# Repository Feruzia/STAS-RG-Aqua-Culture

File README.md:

# STAS-RG-Aqua-Culture
The home base for STAS-RG Aqua Culture research. Covering everything from PCBs and ESP32 code to machine learning.

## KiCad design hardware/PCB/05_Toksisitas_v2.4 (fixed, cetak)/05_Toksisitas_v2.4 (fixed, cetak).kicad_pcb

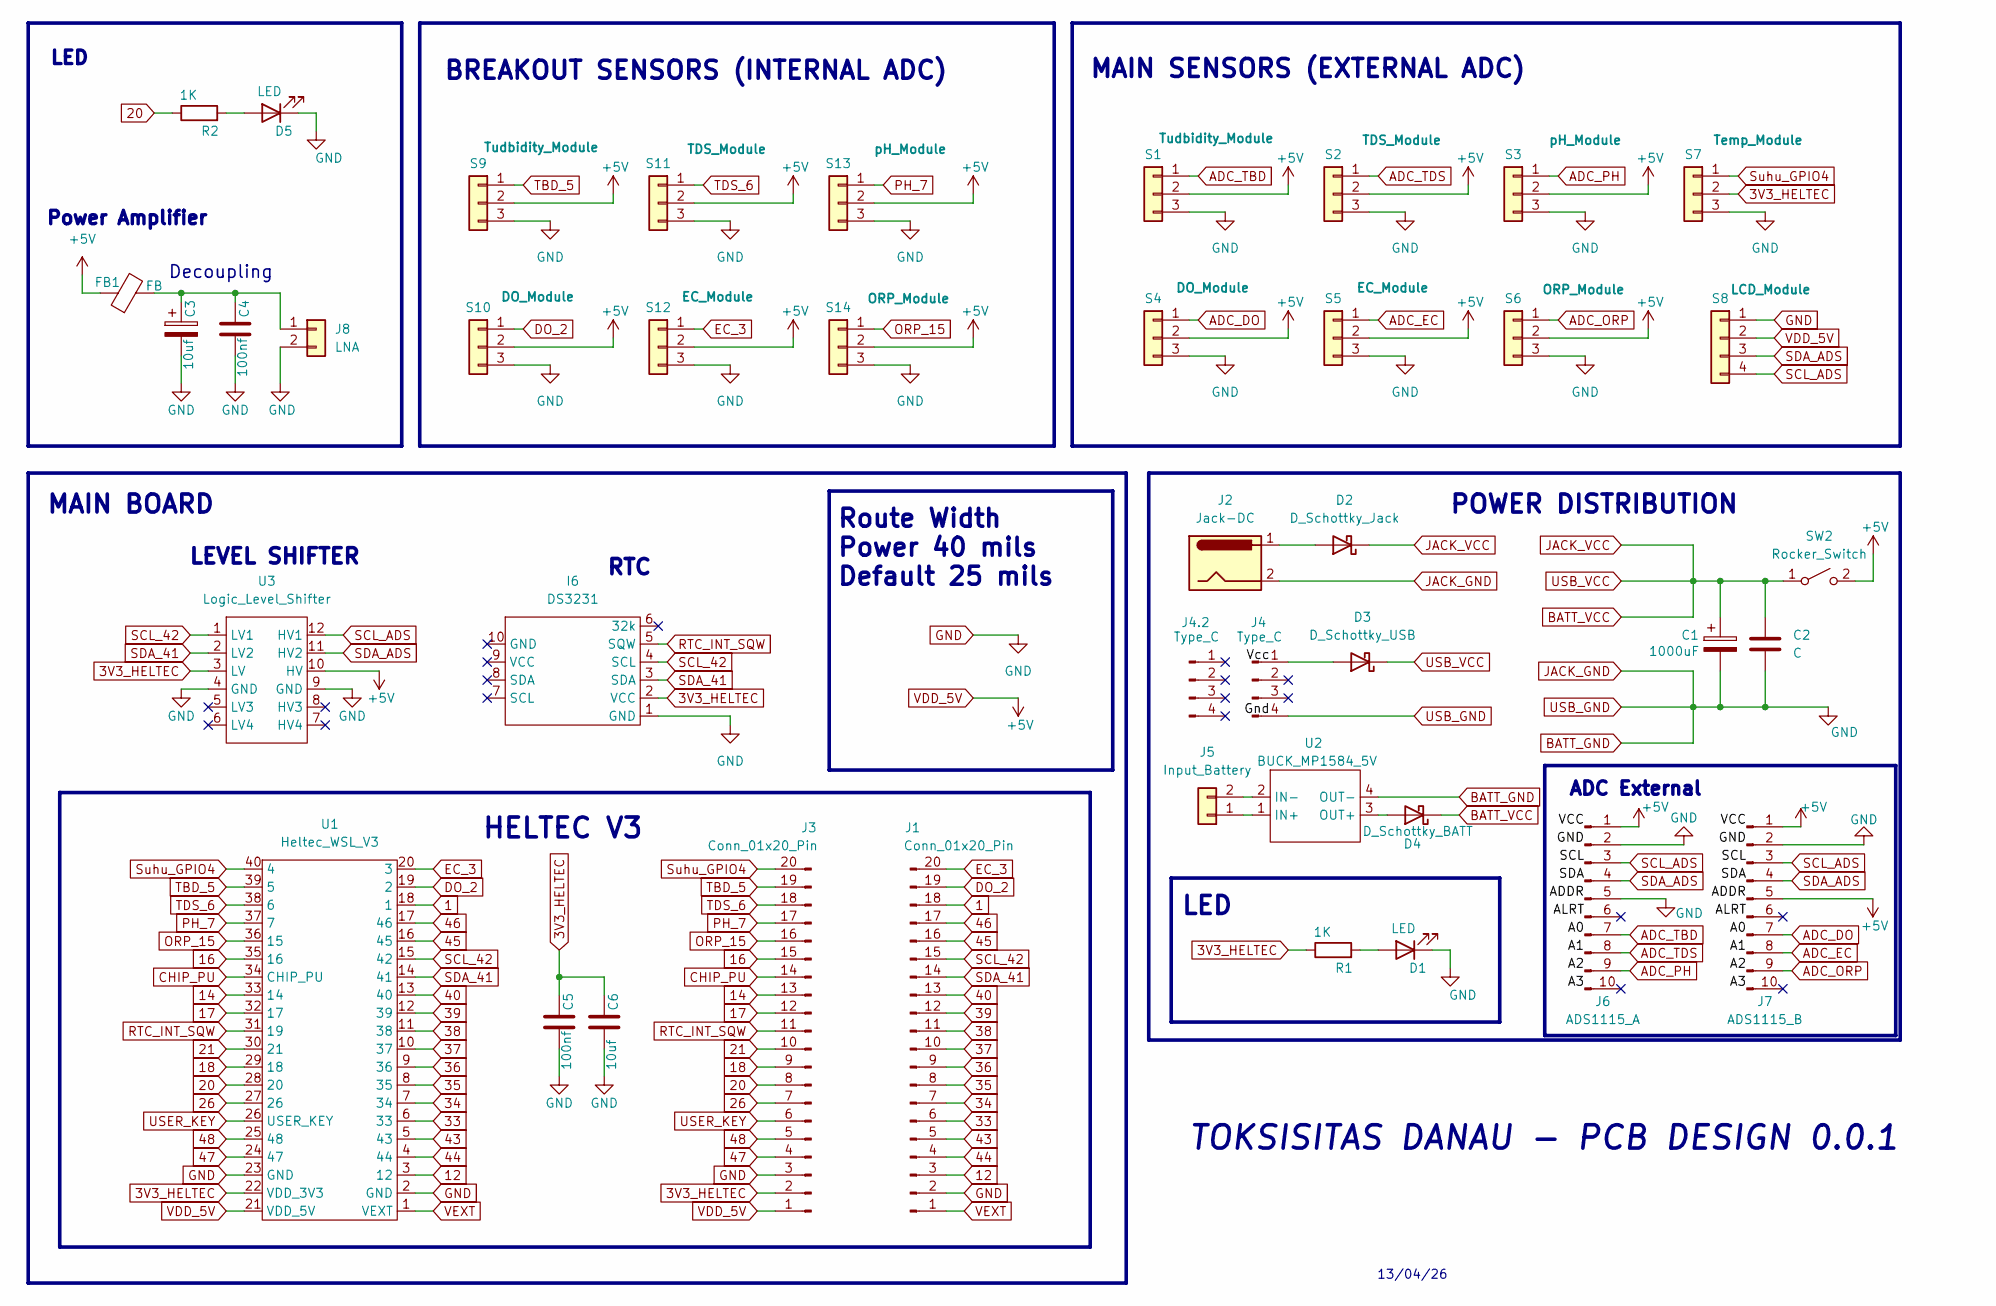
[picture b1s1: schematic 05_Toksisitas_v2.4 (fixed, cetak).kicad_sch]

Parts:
C1: 1000uF; CP_Radial_D10.0mm_P5.00mm
C2: C; C_Disc_D5.0mm_W2.5mm_P2.50mm
C3: 10uf; CP_Radial_D5.0mm_P2.00mm
C4, C5: 100nf; C_Disc_D5.0mm_W2.5mm_P2.50mm
C6: 10uf; C_Disc_D5.0mm_W2.5mm_P2.50mm
D1, D5: LED; LED_D5.0mm
D2: D_Schottky_Jack; D_DO-201AD_P15.24mm_Horizontal
D3: D_Schottky_USB; D_DO-201AD_P15.24mm_Horizontal
D4: D_Schottky_BATT; D_DO-201AD_P15.24mm_Horizontal
FB1: FB; R_Axial_DIN0207_L6.3mm_D2.5mm_P10.16mm_Horizontal
I6: DS3231​; DS3231_Module
J1, J3: Conn_01x20_Pin; PinSocket_1x20_P2.54mm_Vertical
J2: Jack-DC; BarrelJack_Horizontal
J4: Type_C; Type_C_Conn
J4.2: Type_C; PinHeader_1x04_P2.54mm_Vertical
J5: Input_Battery; JST_XH_B2B-XH-A_1x02_P2.50mm_Vertical
J6: ADS1115_A; PinHeader_1x10_P2.54mm_Vertical
J7: ADS1115_B; PinHeader_1x10_P2.54mm_Vertical
J8: LNA; JST_XH_B2B-XH-A_1x02_P2.50mm_Vertical
R1, R2: 1K; R_Axial_DIN0207_L6.3mm_D2.5mm_P7.62mm_Horizontal
S1, S9: Tudbidity_Module; JST_PH_B3B-PH-K_1x03_P2.00mm_Vertical
S2, S11: TDS_Module; JST_PH_B3B-PH-K_1x03_P2.00mm_Vertical
S3, S13: pH_Module; JST_PH_B3B-PH-K_1x03_P2.00mm_Vertical
S4, S10: DO_Module; JST_PH_B3B-PH-K_1x03_P2.00mm_Vertical
S5, S12: EC_Module; JST_PH_B3B-PH-K_1x03_P2.00mm_Vertical
S6, S14: ORP_Module; JST_PH_B3B-PH-K_1x03_P2.00mm_Vertical
S7: Temp_Module; JST_PH_B3B-PH-K_1x03_P2.00mm_Vertical
S8: LCD_Module; JST_XH_B4B-XH-A_1x04_P2.50mm_Vertical
SW2: Rocker_Switch
U1: Heltec_WSL_V3; Heltec_WSL_V3_Module
U2: BUCK_MP1584_5V; BUCK_MP1584_5V_Module
U3: Logic_Level_Shifter; Level_Shifter_Module

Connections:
1: J1.18, U1.18 (1)
3V3_HELTEC: C5.1, C6.1, I6.2 (VCC), J3.2, R1.1, S7.2, U1.22 (VDD_3V3), U3.3 (LV)
12: J1.3, U1.3 (12)
14: J3.13, U1.33 (14)
16: J3.15, U1.35 (16)
17: J3.12, U1.32 (17)
18: J3.9, U1.29 (18)
20: J3.8, R2.1, U1.28 (20)
21: J3.10, U1.30 (21)
26: J3.7, U1.27 (26)
33: J1.6, U1.6 (33)
34: J1.7, U1.7 (34)
35: J1.8, U1.8 (35)
36: J1.9, U1.9 (36)
37: J1.10, U1.10 (37)
38: J1.11, U1.11 (38)
39: J1.12, U1.12 (39)
40: J1.13, U1.13 (40)
43: J1.5, U1.5 (43)
44: J1.4, U1.4 (44)
45: J1.16, U1.16 (45)
46: J1.17, U1.17 (46)
47: J3.4, U1.24 (47)
48: J3.5, U1.25 (48)
ADC_DO: J7.7, S4.1
ADC_EC: J7.8, S5.1
ADC_ORP: J7.9, S6.1
ADC_PH: J6.9, S3.1
ADC_TBD: J6.7, S1.1
ADC_TDS: J6.8, S2.1
BATT_GND: C1.2, C2.2, C3.2, C4.2, C5.2, C6.2, D1.1 (K), D5.1 (K), I6.1 (GND), J1.2, J2.2, J3.3, J4.4, J6.2, J6.5, J7.2, J8.2, S1.3, S2.3, S3.3, S4.3, S5.3, S6.3, S7.3, S8.1, S9.3, S10.3, S11.3, S12.3, S13.3, S14.3, U1.2 (GND), U1.23 (GND), U2.4 (OUT-), U3.4 (GND), U3.9 (GND)
BATT_VCC: C1.1, C2.1, D2.1 (K), D3.1 (K), D4.1 (K), SW2.1 (A)
CHIP_PU: J3.14, U1.34 (CHIP_PU)
DO_2: J1.19, S10.1, U1.19 (2)
EC_3: J1.20, S12.1, U1.20 (3)
unnamed: D1.2 (A), R1.2
unnamed: D2.2 (A), J2.1
unnamed: D3.2 (A), J4.1
unnamed: D4.2 (A), U2.3 (OUT+)
unnamed: D5.2 (A), R2.2
unnamed: J5.1, U2.1 (IN+)
unnamed: J5.2, U2.2 (IN-)
unnamed: C3.1, C4.1, FB1.2, J8.1
ORP_15: J3.16, S14.1, U1.36 (15)
PH_7: J3.17, S13.1, U1.37 (7)
RTC_INT_SQW: I6.5 (SQW), J3.11, U1.31 (19)
SCL_42: I6.4 (SCL), J1.15, U1.15 (42), U3.1 (LV1)
SCL_ADS: J6.3, J7.3, S8.4, U3.12 (HV1)
SDA_41: I6.3 (SDA), J1.14, U1.14 (41), U3.2 (LV2)
SDA_ADS: J6.4, J7.4, S8.3, U3.11 (HV2)
Suhu_GPIO4: J3.20, S7.1, U1.40 (4)
TBD_5: J3.19, S9.1, U1.39 (5)
TDS_6: J3.18, S11.1, U1.38 (6)
USER_KEY: J3.6, U1.26 (USER_KEY)
VDD_5V: FB1.1, J3.1, J6.1, J7.1, J7.5, S1.2, S2.2, S3.2, S4.2, S5.2, S6.2, S8.2, S9.2, S10.2, S11.2, S12.2, S13.2, S14.2, SW2.2 (B), U1.21 (VDD_5V), U3.10 (HV)
VEXT: J1.1, U1.1 (VEXT)

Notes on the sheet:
13/04/26
LEVEL SHIFTER
ADC External
Decoupling
TOKSISITAS DANAU - PCB DESIGN 0.0.1
LED
Power Amplifier
BREAKOUT SENSORS (INTERNAL ADC)
POWER DISTRIBUTION
Route Width Power 40 mils Default 25 mils
MAIN SENSORS (EXTERNAL ADC)
MAIN BOARD
HELTEC V3
RTC

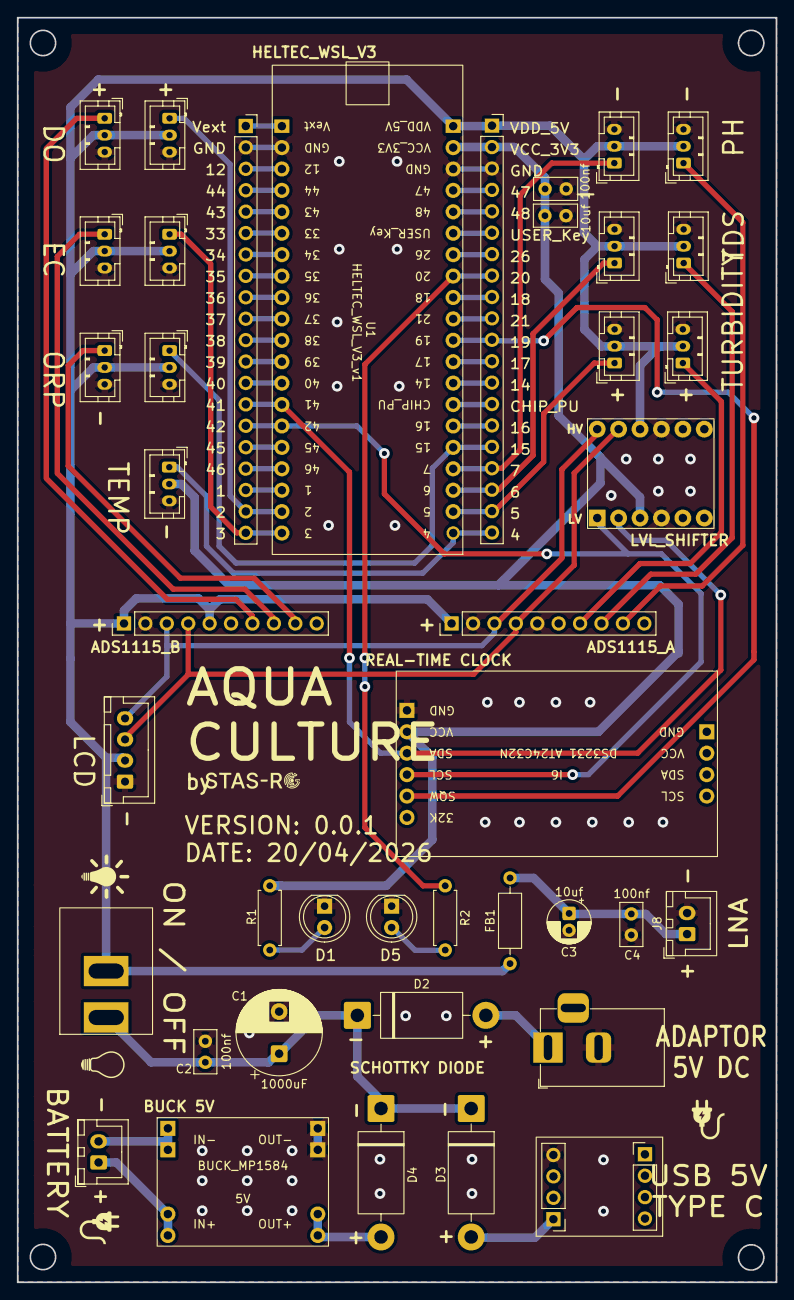
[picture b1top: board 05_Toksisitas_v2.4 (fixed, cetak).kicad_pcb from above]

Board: 2 copper layers, 90.0 x 150.0 mm, 42 parts (0 on the bottom side), 56 nets.

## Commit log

2026-04-30 Update .gitignore with custom additions
    Added custom ignore patterns for firmware, machine learning, and hardware design files.
2026-04-30 Create init
2026-04-30 Create components
2026-05-07 Add files via upload
    Latest code for aqua culture monitoring system
2026-05-07 Tambah file kalibrasi sensor
2026-05-07 Refactor README.md for clarity and formatting
    Updated README.md to improve formatting and remove redundant text.
2026-05-07 Enhance README with sensor details and calibration steps
    Added detailed sensor descriptions and calibration procedures for various water quality sensors used in research.
2026-05-20 lastest master code, changes the K value on EC Val to K=4. Still no web config yet
2026-05-20 Udah sama web dan K val = 4.64 untuk EC
2026-06-30 Lastest PCB
2026-06-30 Create kalibrasi sensor
